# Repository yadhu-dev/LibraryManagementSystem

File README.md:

# Library Management System

## Overview

The Library Management System (LMS) is designed to streamline and modernize library operations by enabling self-service checkouts and returns of books and other materials. This innovative system leverages RFID technology for identifying library items and an Internet of Things (IoT) infrastructure to communicate with a central server. It enhances user experience, reduces manual workload for library staff, and ensures efficient management of library resources.

## Key Features

- **Self-Service Checkouts and Returns:**
  - Users can check out and return books independently, reducing wait times and improving convenience.
  - The system uses RFID tags attached to library items, which can be scanned quickly and easily.

- **RFID Technology:**
  - Each library item is equipped with an RFID tag containing a unique identifier.
  - An RFID reader integrated with an Arduino board reads these tags to capture the item's details.

- **Standalone Application:**
  - The system connects to the local library for fetching necessary details without the need for online dependancy.
  - This eliminates any connectivity issues like latency and downtime.

- **Central Server Communication:**
  - The software sends HTTP requests to a central server to update the local database with checkout and return information.
  - The flask server handles these requests and manages the local library database which is implemented using mysql.

- **Database Integration:**
  - The server stores information about library items, user transactions, and inventory status.
  - This centralized database ensures that the library can track all items and user activities accurately.

## System Components

- **Arduino Board with RFID Reader:**
  - The heart of the system, responsible for reading RFID tags and sending data to the server.
  - Prepares UID for data mapping and it's only function is to fetch UID from the tags.
  - The board is made to be completely replaceable to avoid much of hardware dependancy.

- **Flask Server:**
  - A lightweight web server that reads the serial data from the micro controller and maps the data with the required UIDs.
  - Manages the database and provides APIs for updating item status.
  - Facilitates data mapping according to UID - Data.

- **RFID Tags:**
  - Attached to each library item, these tags store unique identifiers that can be read by the RFID reader.
  - Enable quick and accurate identification of items during checkouts and returns.

# Modules

## Data Mapping Module

1. **User Interaction:**
   - Users scan their library card (RFID tag) and the items they wish to check out or return.
   - The RFID reader captures the UID from the tag and prints it serially.

2. **Data Transmission:**
   - The serial data is read by the flask backend and printed on the frontend for data mapping.
   - The user can give the roll number that should be mapped to the UID received.
   - On submission, if no duplicates exist, push to the database and show confirmation.

3. **Server Processing:**
   - On receiving the mapped data, sends it to the flask server to store it in the local database.
   - The server sends a response back to the frontend to tell the user that the details has been updated.

## CRUD Module

1. **User Interaction:**
   - A table with all the registered users will be shown on the page loading.
   - The user can tap the RFID tag to search for the data associated with the UID scanned.
   - The user can perform the crud operation required and save changes to the local dataabse.

2. **Server Processing:**
   - On reading the RFID card, the data is sent serially to the backend for filtering the user.
   - The user data associated with the UID can be updated or deleted.
   - The updated data gets sent back to the flask backend to be updated in the local database.

## Keystroke Module

1. **User Interaction:**
   - The user can change the data mapping mode to keystroke mode by clicking the start keystroke button.
   - When this mode is active, the roll no or any number associated with the UID read will be printed on any input field as keystrokes.
   - This is useful for easily fetching the indentifying data through the UID of the tag without manually entering it.

2. **Data Transmission:**
   - The serial data is read by the flask backend and the associated data is fetched.
   - The data is typed on the focused input field as keystrokes for the use case.
   - No data is typed if the UID is not mapped.

3. **Server Processing:**
   - On activating keystroke mode, the data mapping mode ceases temporarily to avoid read clashes.
   - The serial data is read and the associated data is fetched and stored for typing.
   - On finding an input field, the data is typed in string format in the form of keystrokes and presses enter if necessary.

# Installation

  - Run `Installer.bat` as administrator as it installes all the software dependencies and packages required for the program to function.
  - If any super user prompt, click allow since it needs to install python and mysql which requires additional administrative privilages.
  - If installer fails, do the following:

    1. Install python 

# Benefits

- **Efficiency:** Automates the checkout and return process, reducing manual workload and speeding up operations.
- **User Convenience:** Allows users to manage their library transactions independently, enhancing their experience.
- **Accuracy:** Ensures precise tracking of library items, reducing the chances of errors and lost items.
- **Real-Time Updates:** Keeps the library inventory updated in real-time, ensuring accurate availability information.

This Library Management System represents a significant step forward in library automation, leveraging modern technology to improve service delivery and operational efficiency.

# PCB Schematic Diagram

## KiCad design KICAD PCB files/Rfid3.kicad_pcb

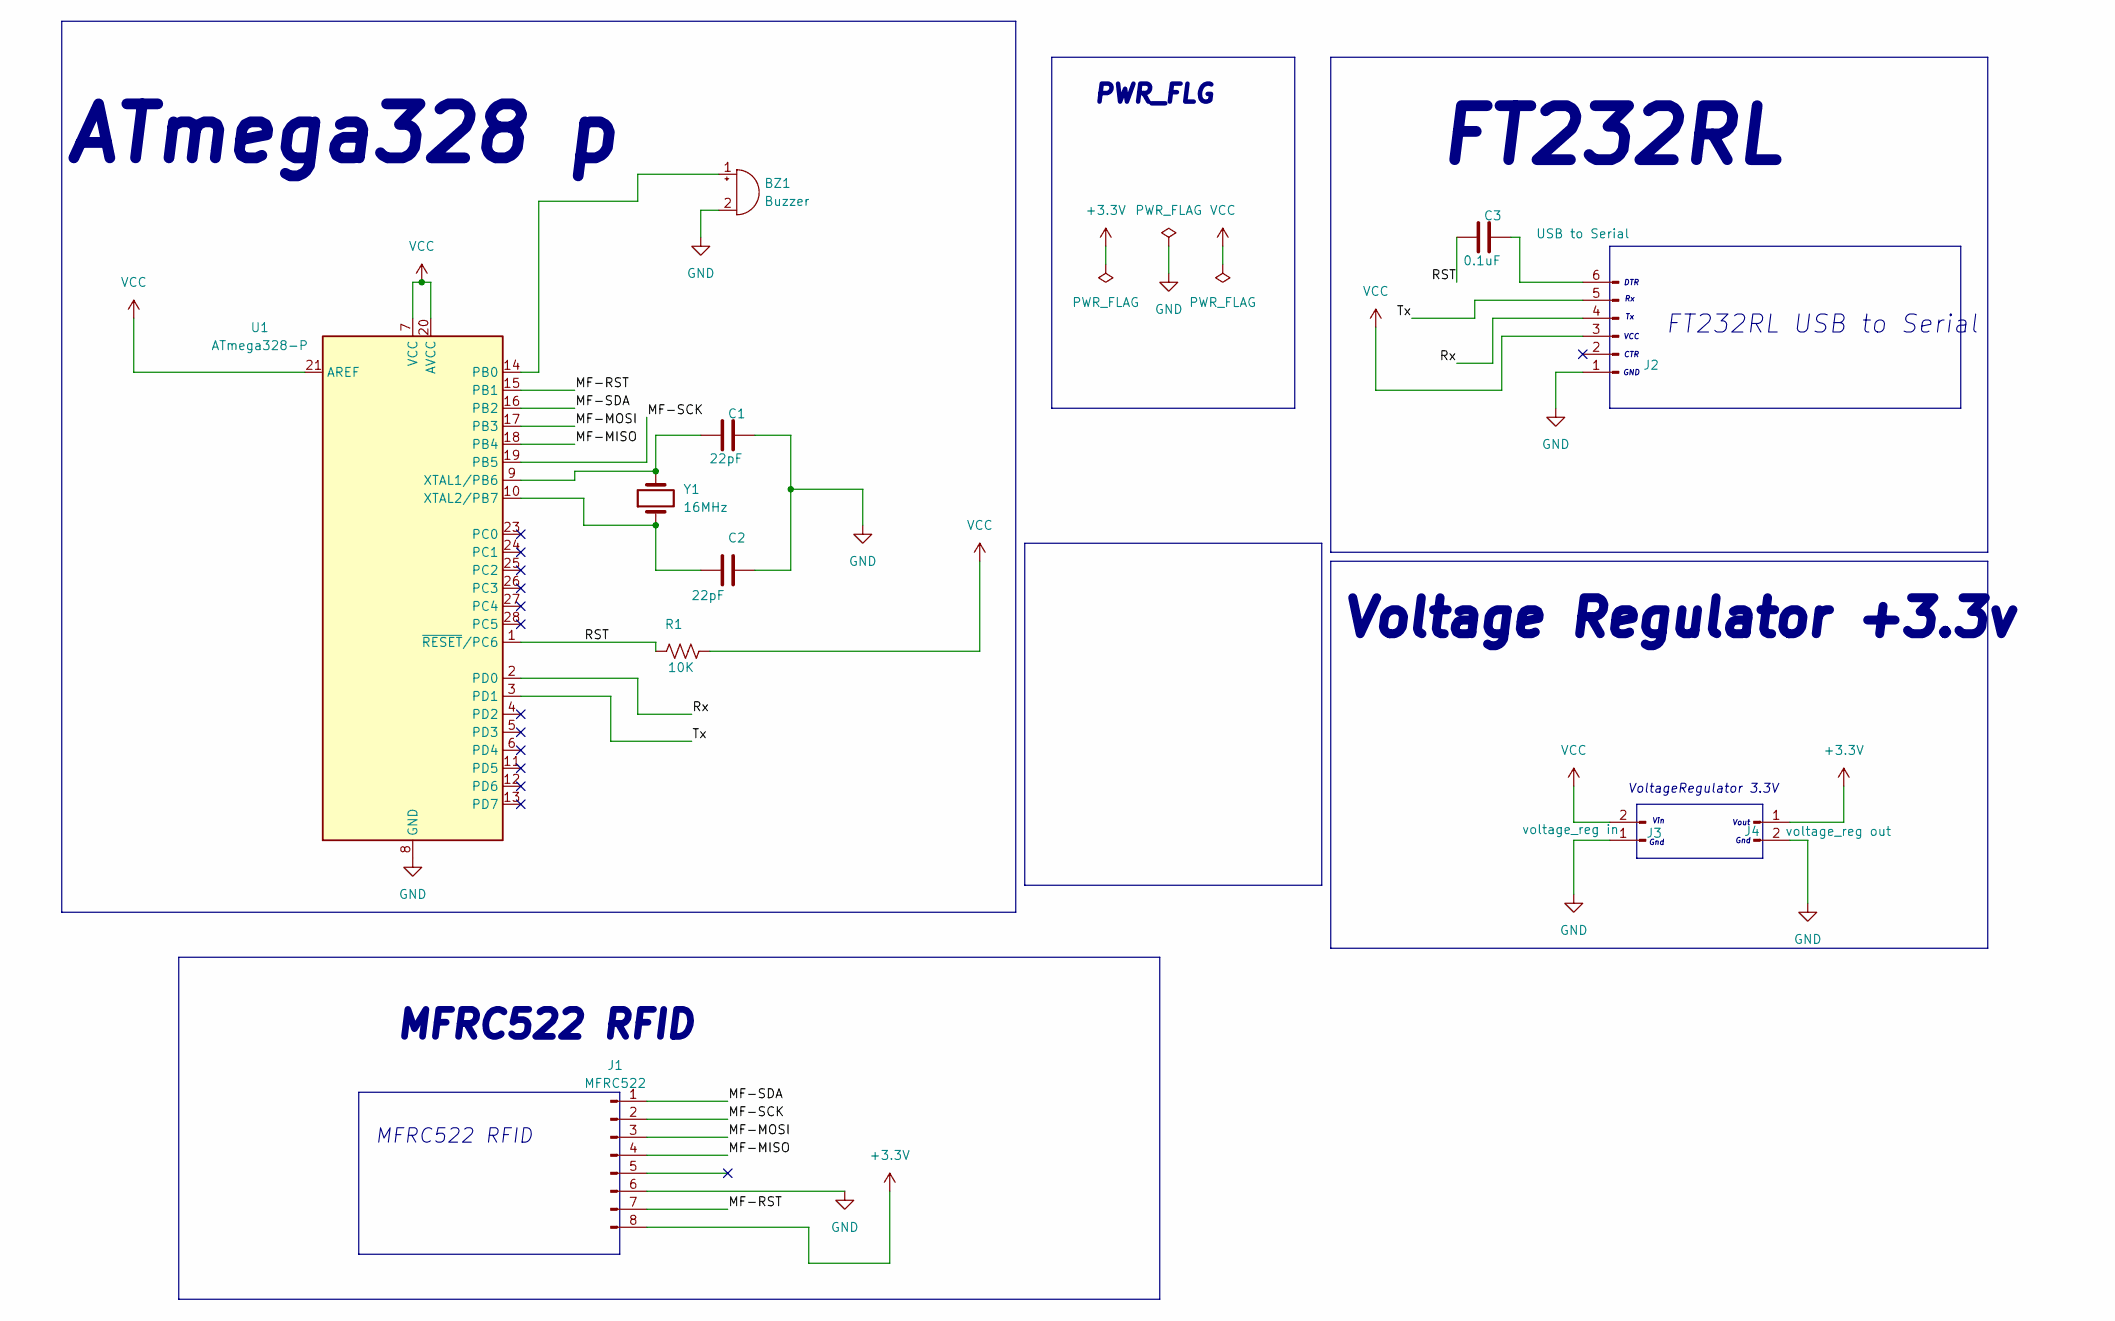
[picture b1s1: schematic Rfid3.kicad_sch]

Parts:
BZ1: Buzzer; Buzzer_TDK_PS1240P02BT_D12.2mm_H6.5mm
C1, C2: 22pF; C_Disc_D3.8mm_W2.6mm_P2.50mm
C3: 0.1uF; C_Disc_D3.8mm_W2.6mm_P2.50mm
J1: MFRC522; PinHeader_1x08_P2.54mm_Vertical
J2: USB to Serial; PinHeader_1x06_P2.54mm_Vertical
J3: voltage_reg in; PinHeader_1x02_P2.54mm_Vertical
J4: voltage_reg out; PinHeader_1x02_P2.54mm_Vertical
R1: 10K; R_Axial_DIN0204_L3.6mm_D1.6mm_P5.08mm_Horizontal
U1: ATmega328-P; DIP-28_W7.62mm
Y1: 16MHz; Crystal_HC49-4H_Vertical

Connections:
+3.3V: J1.8, J4.1
/MF-MISO: J1.4, U1.18 (PB4)
/MF-MOSI: J1.3, U1.17 (PB3)
/MF-RST: J1.7, U1.15 (PB1)
/MF-SCK: J1.2, U1.19 (PB5)
/MF-SDA: J1.1, U1.16 (PB2)
/RST: C3.1, R1.1, U1.1 (~RESET/PC6)
/Rx: J2.4, U1.2 (PD0)
/Tx: J2.5, U1.3 (PD1)
GND: BZ1.2 (-), C1.2, C2.2, J1.6, J2.1, J3.1, J4.2, U1.8 (GND), U1.22 (GND); also elsewhere on the board
unnamed: BZ1.1 (+), U1.14 (PB0)
unnamed: C3.2, J2.6
unnamed: C1.1, U1.9 (XTAL1/PB6), Y1.2
unnamed: C2.1, U1.10 (XTAL2/PB7), Y1.1
VCC: J2.3, J3.2, R1.2, U1.7 (VCC), U1.20 (AVCC), U1.21 (AREF); also elsewhere on the board

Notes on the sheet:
MFRC522 RFID
VoltageRegulator 3.3V
Gnd
Voltage Regulator +3.3v
FT232RL USB to Serial
FT232RL
VCC
CTR
Vout
Vin
DTR
GND
PWR_FLG
ATmega328 p

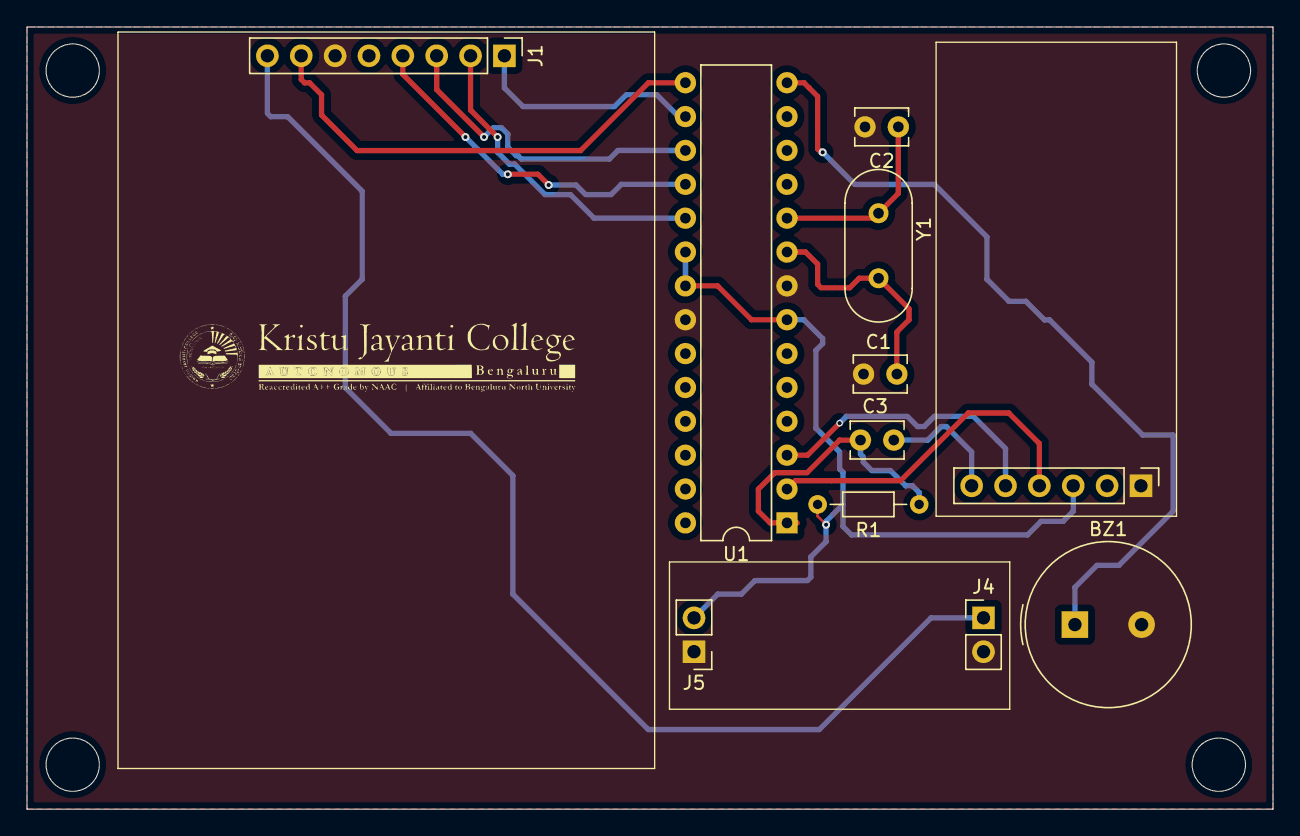
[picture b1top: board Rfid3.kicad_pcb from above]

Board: 2 copper layers, 93.5 x 58.7 mm, 11 parts (0 on the bottom side), 15 nets.

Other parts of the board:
J5: voltage_reg in; PinHeader_1x02_P2.54mm_Vertical

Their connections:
GND: J5.1; also elsewhere on the board
VCC: J5.2; also elsewhere on the board

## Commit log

2024-06-06 Added server and esp code
    - added the esp function to take uid and rollnumber and send it to the expressjs server.
    - added the webserver to read the data sent from the board
2024-06-06 Update README.md
    Added project details and more.
2024-06-07 Added indicators
2024-06-07 minor code changes
2024-06-10 Changed Dir
2024-06-10 Code structure change and updates
    - Switched to localDB to eliminate network issues.
    - Added all the files required.
    - Coded the python program to take input from esp, check for uid in DB, return the rollno and write that rollno in a focused textbox.
2024-06-10 ESP code added
    - Added the esp code to facilitate RFID reading.
    - Added all the necessary comments required.
2024-06-10 Added datamapping.py with basic codes
2024-06-10 fixed the datatype
2024-06-10 moved the datamapping
2024-06-10 added auto serial port detection
2024-06-10 added a loop for scanning the card
2024-06-10 Bug fixes
2024-06-10 test
2024-06-10 fixed the data insertion
2024-06-10 imported time
2024-06-10 conflict resolve
2024-06-10 Flask implementation for UI
    - Added a UI folder which hosts the UI for the reader application.
    - Added a common requirements file.
2024-06-10 Added templates
    - Added templates to use custom web pages.
2024-06-11 fixed the input type
2024-06-11 basic html page done
2024-06-11 html page with css and js
2024-06-11 Adding the getUID endpoint
    - Adding get_uid endpoint to periodically retrieve data from the reader to the webpage.
2024-06-11 Auto fetch UID
    - Scanned tag's UID gets updated in the UID space automatically.
2024-06-11 Functions to send user input
    - Added a js function to send the roll number and uid to the flask server for data mapping.
    - Added a server side endpoint to handle the post request and insert the received data.
2024-06-11 Data Mapping implementation
    - Added functionality to submit button to post UID and Rollno onto the flask server for data insertion and mapping.
    - Added functionality to postData() to receive UID and Rollno and map the data in the local database accordingly.
2024-06-11 Updated the html
2024-06-11 Alerts added
2024-06-11 'Enter' after keystroke entry
2024-06-12 Added indicators
    - Added LED and Buzzer indicators while scanning
2024-06-12 Added Keystroke function
    - Added an iterative function to handle scans and subsequent entry.
2024-06-12 Added a stop condition
    - Added functions to handle stop condition to stop the keystroke entries.
    - Modified the code to accommodate stop thread event.
2024-06-12 Rollback
    - Rolled back the flask code since it broke the uid fetching function
    - Fixed the esp code to avoid false UIDs
2024-06-12 CRUD functions page
2024-06-13 Javascript for keystroke data
    - Function to send the UID for search and keystroke entry function.
2024-06-13 Semi State
    - Enters roll no twice (uses old data
    - Saving for later
2024-06-13 Added Keystroke entry functionality
    - Fixed keystroke entry and db searching functions.
    - Added delay to avoid read clashes.
2024-06-13 Write Control
    - Added controls to the search and keystroke entry function along with the cross communication fixes.
    - Minor bug fixes.
2024-06-18 Test phase start
    - Implementing commercial reader
2024-06-19 Half baked code
2024-06-19 Added a digit filter
    - Digit filter for false positive mitigation
2024-06-19 Adding necessary methods
    - Insert into DB method
    - Fetch from DB method
2024-06-19 Flask Functionalities
    - Added flask endpoints.
    - Added method implementations with the flask app.
    - Functionality to read UID from tag and print on the input field.
    - Functionality to write data into the database.
2024-06-19 Write Function (bugged)
    - Writes and replaces the entry by the commercial reader.
    Bug: first write gets properly changed, second write gets a false reading due to the replacement entry merging with the new entry.
2024-06-20 Pynput application
    - Used Pynput instead of Keyboard library.
    - Added a timeout function to clear the read data to avoid merging.
    - Works in excel
2024-06-25 Added comments to html codes
2024-06-26 File structure corrections
2024-06-26 Convenience update
    - Code segregation for simplicity and better file structure.
    - Updating README.md to accommodate requirement changes.
    - Adding an installer batch file for one click installation of required packages and the necessary setups.
2024-06-26 Update README.md
    - Corrected the formatting.
    - Added docs for keystroke mode.
2024-06-26 File system changes
2024-06-27 Implemented tailwindcss
2024-06-28 Started working on new web design
2024-07-01 removed tailwind files cuz it was not working properly and imported tailwind using script and started with new web page
2024-07-01 Update Installer.bat
    may need changes
2024-07-02 wip webpage
2024-07-02 fixed the scaling of home page
2024-07-02 One Click Installer
    - Added an installer that will set up all the requirements for the code to run.
    - File structure changes.
    - Anti-theft start
2024-07-02 work in progress login popup
2024-07-02 made the popup for login
2024-07-02 Data mapping page
    - Linked javascript to new design.
    - Added the data mapping page.
2024-07-02 made the mapping page, still working on it. need to map the page with nev bar
2024-07-03 made homepage responsive
2024-07-03 fixed the bg-image and nav bar
2024-07-03 Linking new page with the script
    - Linked the new html page to the main script.
    - Click function bugged, have to ctrl+click to load.
2024-07-03 Update espCode.CPP
    - POST request functionality added
2024-07-03 completed the mapping page responsive
2024-07-03 made few changes to homepage (style only)
2024-07-04 File Structure and Functionality
    - Split JS for homepage and mapping page.
    - Linked JS for the new mapping page.
    - Renamed script.js to home.js.
2024-07-04 Crud page
    - Added crud page and crud JS.
    - Fixed the ctrl+click bug.
2024-07-04 did the basic styling for crud page
2024-07-05 Slight changes
2024-07-05 Fixed the variable in home.js
2024-07-06 Functional Crud Page
    - Added a crud page.
    - Display data function added.
    - Update data function added.
    - Delete data function added.
2024-07-07 Login function added
2024-07-08 removed the ovrflow-y-hidden
2024-07-08 Few changes to login.js
2024-07-21 Attendance.py
2024-08-10 To Read all Blocks in ISO15693 RFID tags
2024-08-10 To Read 3rd Block Written Data
2024-08-10 To Write Data in 3rd block ( ISO15693 )
2024-08-10 To Read 3rd block written Data
2024-08-10 To Write Data in 3rd Block
2024-08-10 PN5180 Rfid_readers-Arduino Schematic
2024-08-11 Arduino to PN5180 RFID Reader
2024-08-11 Circuit Digram of PN5180 RFID Reader to Arduino
2024-08-11 How to use Gerber file for PCB manufacture
2024-08-11 Gerber file for PCB
2024-08-11 KICAD files
2024-08-11 README.md
2024-08-13 KeyStroke.py
2024-08-13 Used for AtMega328P
2024-08-13 Python Backend program for KeyStroke
2024-08-22 All_Block_Write.ino
